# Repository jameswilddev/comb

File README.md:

# Comb

A low parts, low cost, low complexity game board compatible with some arcade cabinets.  So named as the PCB somewhat resembles a comb.

## Contents

- [Comb Arcade Breakout Board](./src/comb-arcade-breakout-board/readme.md) - A simple PCB which breaks the arcade connector out to 2.54mm pin headers or sockets, for prototyping purposes.
- [Comb Board](./src/comb-board/readme.md) - A game PCB which fits directly into the arcade connector.
- [Engine][./src/engine/readme.md] - A simplistic games engine.
- [Games][./src/games/readme.md] - A collection of small example games.

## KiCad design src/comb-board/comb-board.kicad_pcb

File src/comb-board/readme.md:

# [Comb](../../README.md) > Board

This is a game PCB which fits directly into the arcade connector.

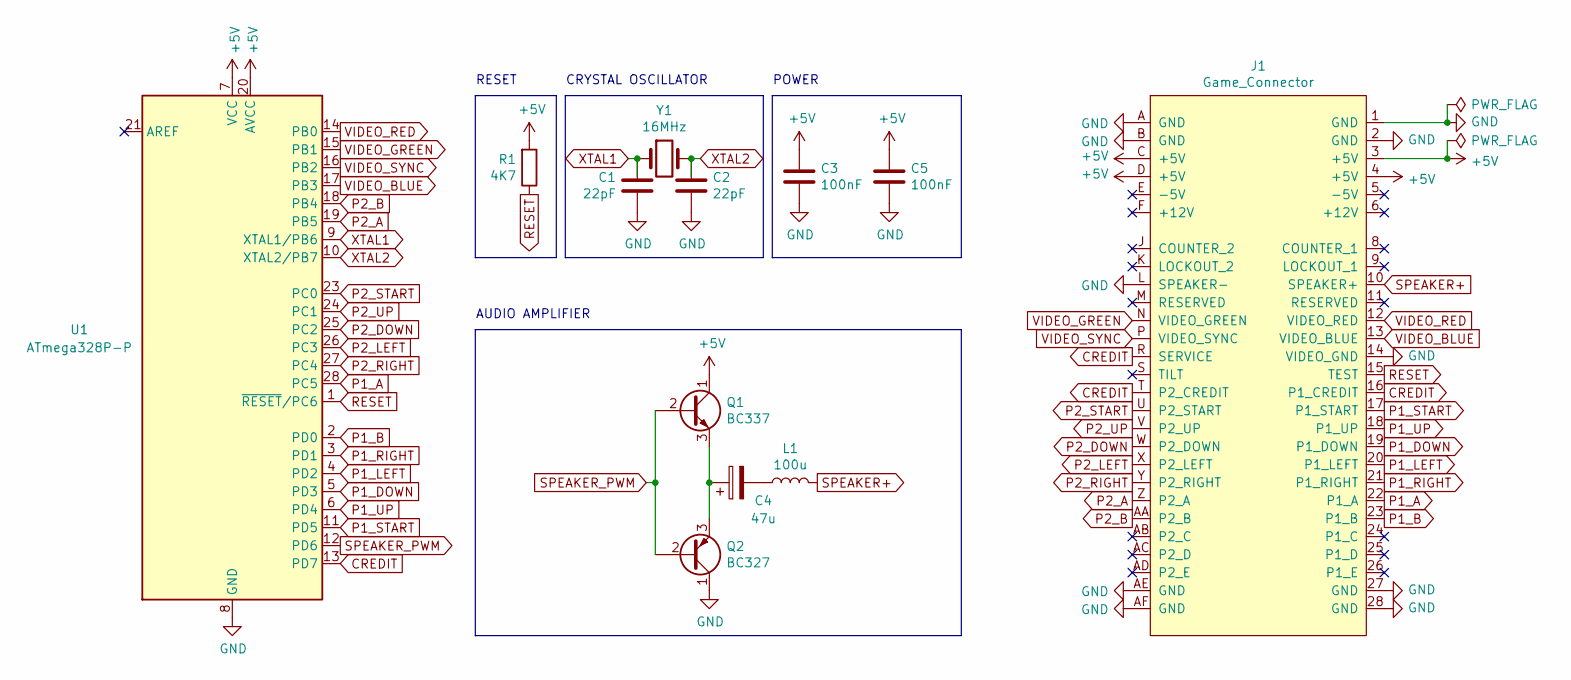
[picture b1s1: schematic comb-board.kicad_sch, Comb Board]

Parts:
C1, C2: 22pF; C_Disc_D3.0mm_W1.6mm_P2.50mm
C3, C5: 100nF; C_Disc_D3.0mm_W1.6mm_P2.50mm
C4: 47u; CP_Radial_D6.3mm_P2.50mm
J1: Game_Connector; Edge_Connector
L1: 100u; L_Radial_D7.5mm_P5.00mm_Fastron_07P
Q1: BC337; TO-92_Inline
Q2: BC327; TO-92_Inline
R1: 4K7; R_Axial_DIN0204_L3.6mm_D1.6mm_P7.62mm_Horizontal
U1: ATmega328P-P; DIP-28_W7.62mm
Y1: 16MHz; Crystal_HC49-4H_Vertical

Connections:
+5V: C3.2, C5.2, J1.3 (+5V), J1.4 (+5V), J1.C (+5V), J1.D (+5V), Q1.1 (C), R1.2, U1.7 (VCC), U1.20 (AVCC)
CREDIT: J1.16 (P1_CREDIT), J1.R (SERVICE), J1.T (P2_CREDIT), U1.13 (PD7)
GND: C1.1, C2.1, C3.1, C5.1, J1.1 (GND), J1.2 (GND), J1.14 (VIDEO_GND), J1.27 (GND), J1.28 (GND), J1.A (GND), J1.AE (GND), J1.AF (GND), J1.B (GND), J1.L (SPEAKER-), Q2.1 (C), U1.8 (GND), U1.22 (GND)
unnamed: C4.1, Q1.3 (E), Q2.3 (E)
unnamed: C4.2, L1.1
P1_A: J1.22 (P1_A), U1.28 (PC5)
P1_B: J1.23 (P1_B), U1.2 (PD0)
P1_DOWN: J1.19 (P1_DOWN), U1.5 (PD3)
P1_LEFT: J1.20 (P1_LEFT), U1.4 (PD2)
P1_RIGHT: J1.21 (P1_RIGHT), U1.3 (PD1)
P1_START: J1.17 (P1_START), U1.11 (PD5)
P1_UP: J1.18 (P1_UP), U1.6 (PD4)
P2_A: J1.Z (P2_A), U1.19 (PB5)
P2_B: J1.AA (P2_B), U1.18 (PB4)
P2_DOWN: J1.W (P2_DOWN), U1.25 (PC2)
P2_LEFT: J1.X (P2_LEFT), U1.26 (PC3)
P2_RIGHT: J1.Y (P2_RIGHT), U1.27 (PC4)
P2_START: J1.U (P2_START), U1.23 (PC0)
P2_UP: J1.V (P2_UP), U1.24 (PC1)
RESET: J1.15 (TEST), R1.1, U1.1 (~RESET/PC6)
SPEAKER+: J1.10 (SPEAKER+), L1.2
SPEAKER_PWM: Q1.2 (B), Q2.2 (B), U1.12 (PD6)
VIDEO_BLUE: J1.13 (VIDEO_BLUE), U1.17 (PB3)
VIDEO_GREEN: J1.N (VIDEO_GREEN), U1.15 (PB1)
VIDEO_RED: J1.12 (VIDEO_RED), U1.14 (PB0)
VIDEO_SYNC: J1.P (VIDEO_SYNC), U1.16 (PB2)
XTAL1: C1.2, U1.9 (XTAL1/PB6), Y1.1
XTAL2: C2.2, U1.10 (XTAL2/PB7), Y1.2

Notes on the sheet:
RESET
AUDIO AMPLIFIER
CRYSTAL OSCILLATOR
POWER

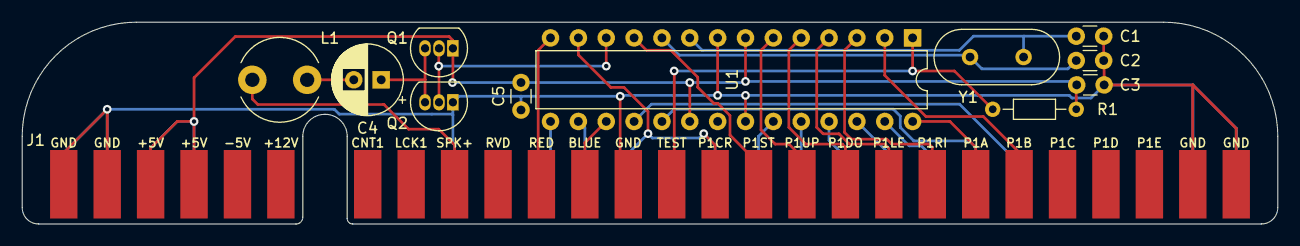
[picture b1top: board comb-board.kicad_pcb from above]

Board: 2 copper layers, 114.5 x 18.4 mm, 12 parts (0 on the bottom side), 28 nets.

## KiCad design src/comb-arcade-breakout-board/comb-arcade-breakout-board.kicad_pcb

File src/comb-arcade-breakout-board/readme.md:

# [Comb](../../README.md) > Arcade Breakout Board

This is a simple PCB which breaks the arcade connector out to 2.54mm pin headers or sockets, for prototyping purposes.

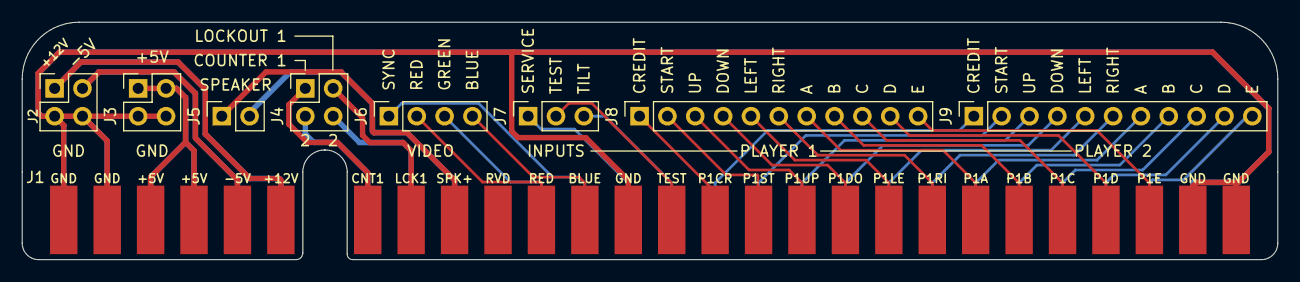
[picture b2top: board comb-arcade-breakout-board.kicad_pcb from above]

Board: 2 copper layers, 114.5 x 21.7 mm, 9 parts (0 on the bottom side), 39 nets.

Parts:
J1: Game_Connector; Edge_Connector
J2: PWR_DANGEROUS; PinSocket_2x02_P2.54mm_Vertical
J3: PWR_SAFE; PinSocket_2x02_P2.54mm_Vertical
J4: COIN_SLOTS; PinSocket_2x02_P2.54mm_Vertical
J5: SPEAKER; PinSocket_1x02_P2.54mm_Vertical
J6: VIDEO; PinSocket_1x04_P2.54mm_Vertical
J7: MISC_INPUTS; PinSocket_1x03_P2.54mm_Vertical
J8: P1; PinSocket_1x11_P2.54mm_Vertical
J9: P2; PinSocket_1x11_P2.54mm_Vertical

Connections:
+5V: J1.3, J1.4, J1.C, J1.D, J3.1, J3.3
+12V: J1.6, J1.F, J2.1
-5V: J1.5, J1.E, J2.3
COUNTER_1: J1.8, J4.1
COUNTER_2: J1.J, J4.2
GND: J1.1, J1.2, J1.14, J1.27, J1.28, J1.A, J1.AE, J1.AF, J1.B, J2.2, J2.4, J3.2, J3.4
LOCKOUT_1: J1.9, J4.3
LOCKOUT_2: J1.K, J4.4
P1_A: J1.22, J8.7
P1_B: J1.23, J8.8
P1_C: J1.24, J8.9
P1_CREDIT: J1.16, J8.1
P1_D: J1.25, J8.10
P1_DOWN: J1.19, J8.4
P1_E: J1.26, J8.11
P1_LEFT: J1.20, J8.5
P1_RIGHT: J1.21, J8.6
P1_START: J1.17, J8.2
P1_UP: J1.18, J8.3
P2_A: J1.Z, J9.7
P2_B: J1.AA, J9.8
P2_C: J1.AB, J9.9
P2_CREDIT: J1.T, J9.1
P2_D: J1.AC, J9.10
P2_DOWN: J1.W, J9.4
P2_E: J1.AD, J9.11
P2_LEFT: J1.X, J9.5
P2_RIGHT: J1.Y, J9.6
P2_START: J1.U, J9.2
P2_UP: J1.V, J9.3
SERVICE: J1.R, J7.1
SPEAKER+: J1.10, J5.1
SPEAKER-: J1.L, J5.2
TEST: J1.15, J7.2
TILT: J1.S, J7.3
VIDEO_BLUE: J1.13, J6.4
VIDEO_GREEN: J1.N, J6.3
VIDEO_RED: J1.12, J6.2
VIDEO_SYNC: J1.P, J6.1

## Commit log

2021-05-02 Add gitattributes.
2021-05-02 Add shared footprints and symbols.
2021-05-02 Add arcade breakout board.
2021-05-02 Do not commit Gerber files.
2021-05-02 First attempt at KiCAD exports in CI.
2021-05-02 Add standard settings file.
2021-05-02 Fix workflow.
2021-05-02 Try an alternative.
2021-05-02 Specify optional parameters.
2021-05-02 Adjust wildcard.
2021-05-02 Looks like wildcards don't work.
2021-05-02 Try an example.
2021-05-02 Try without wildcards.
2021-05-02 Enable verbose output.
2021-05-02 Fix typo.
2021-05-02 Use configurations from actions.
2021-05-02 Change exports.
2021-05-02 Disable verbose.
2021-05-02 Remove debug output.
2021-05-02 Include all zip files in builds.
2021-05-02 Fix parsing error.
2021-05-02 Reconfigure.
2021-05-02 Fix misalignements on comb PCB.
2021-05-02 Exclude cache files.
2021-05-02 Adjust label.
2021-05-02 Fix label cropping.
2021-05-09 Move PCB design under a src directory.
2021-05-09 Add license.
2021-05-11 Add some basic documentation.
2021-05-11 Rename workflow.
2021-05-11 Install dependencies for CI.
2021-05-11 Add minimal games.
2021-05-11 Begin adding engine.
2021-05-11 Add electrical considerations.
2021-05-24 Fix paths.
2021-05-24 Rename FREE CREDIT to SERVICE.
2021-05-24 Initial game board design.
2022-06-26 Add renovate.json
2022-07-14 Upgrade KiCAD.
2022-07-14 Update CI.
2022-07-14 Upgrade to compatible version.
2022-07-14 Add config files.
2022-07-14 Fix DRC.
2022-08-10 Do not commit backup archives.
2022-08-10 Exclude from VSC.
2022-08-10 Attempt to fix CI.
2022-08-10 Update actions/checkout action to v3
2022-08-10 Check outputs.
2022-08-10 Continue debugging.
2022-08-10 Zip files.
2022-08-10 Workaround for permissions issue.
2022-08-10 Update INTI-CMNB/KiBot action to v2
